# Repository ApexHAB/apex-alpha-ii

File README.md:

# Apex Alpha II
## A tiny, light-weight 'pico' flight computer with potential applications as a balloon neck payload

The flight computer is based around a CC430 microcontroller and radio by Texas Instruments with a uBlox Max-6.
It runs off a single AAA battery.

## Useful links

* [Homepage](http://www.apexhab.org) - http://www.apexhab.org
* [Apex Alpha II Homepage](http://www.apexhab.org/alpha-ii/) - http://www.apexhab.org/alpha-ii/
* [Contact](mailto:team@apexhab.org) - team@apexhab.org
* [Twitter](http://twitter.com/apexhab) - http://twitter.com/apexhab

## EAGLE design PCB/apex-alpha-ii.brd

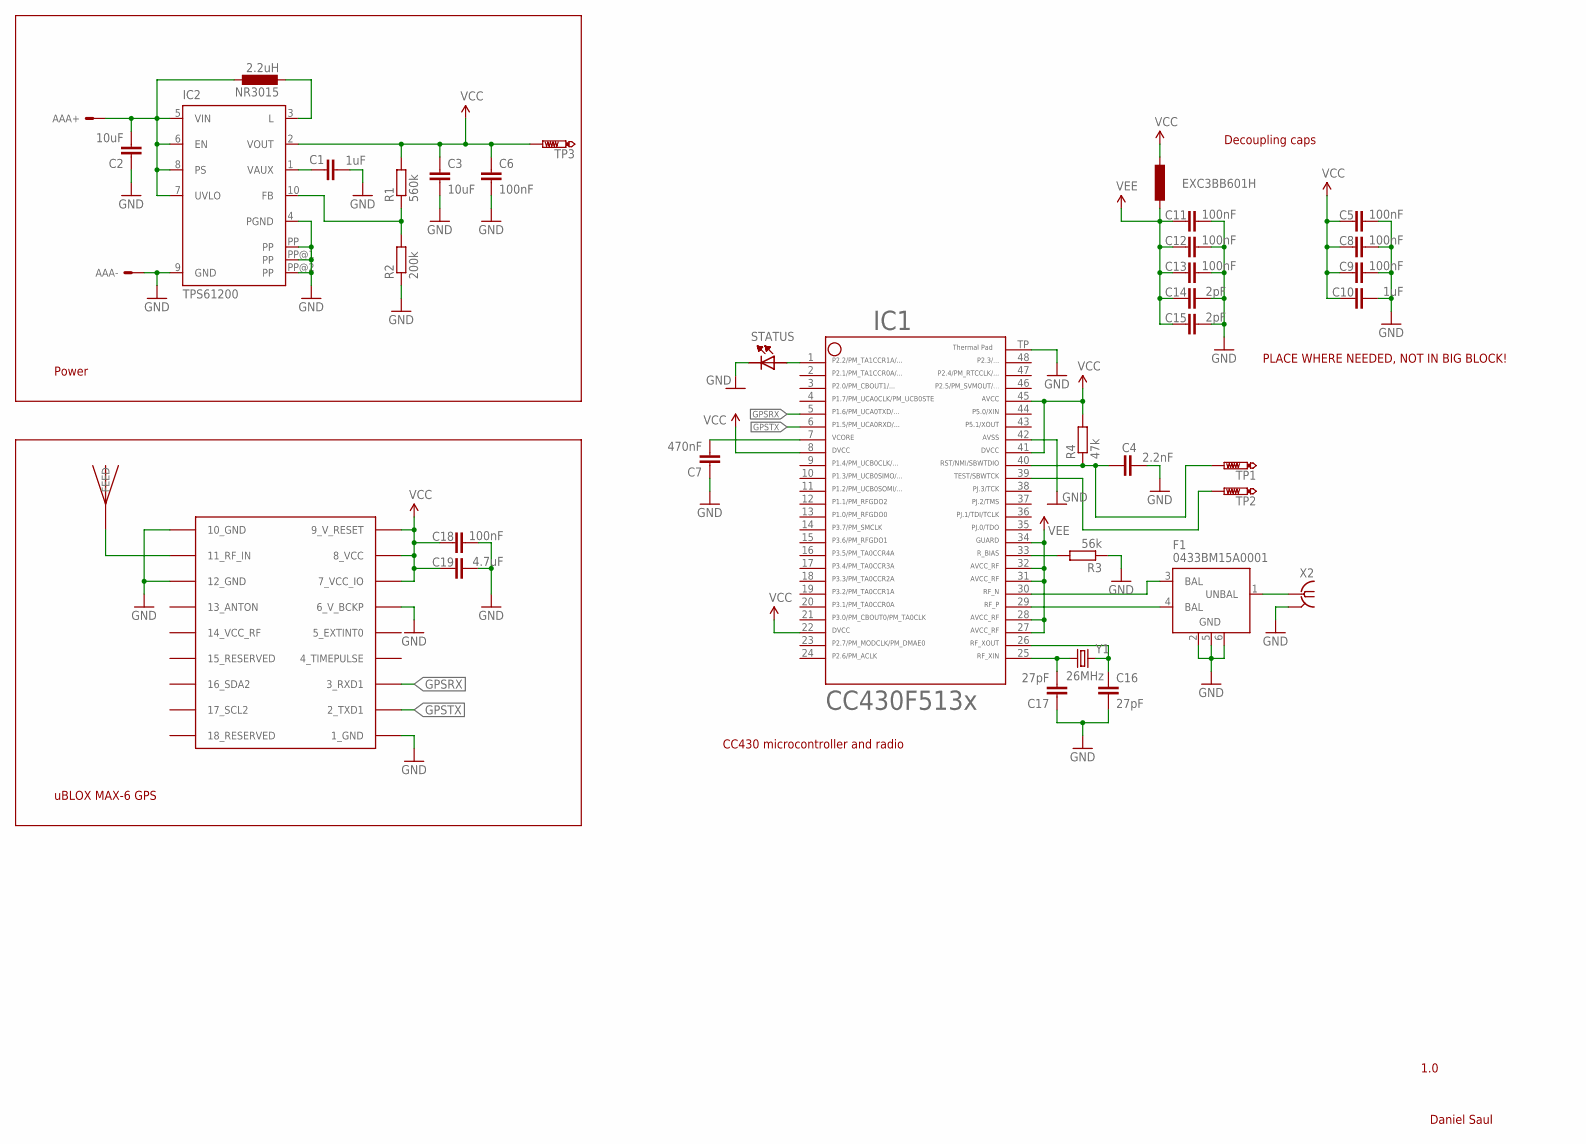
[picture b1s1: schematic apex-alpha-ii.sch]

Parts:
AAA: KEYSTONE-2466-THROUGH-HOLE-BATTERY-HOLDER-AAA; THROUGH-HOLE-BATTERY-HOLDER-AAA
C1, C10: 1uF; 0402-CAP
C2, C3: 10uF; 0805
C4: 2.2nF; 0402-CAP
C5, C6, C8, C9, C11, C12, C13, C18: 100nF; 0402-CAP
C7: 470nF; 0402-CAP
C14, C15: 2pF; 0402-CAP
C16, C17: 27pF; 0402-CAP
C19: 4.7uF; 0805
F1: 0433BM15A0001; 2450BM15A0002
GPS: UBLOX_MAX-6
IC1: CC430F5135; RGZ48
IC2: TPS61200; S-PDSO-N10
NR3015: 2.2uH; NR3015
R1: 560k; R0402
R2: 200k; R0402
R3: 56k; R0402
R4: 47k; R0402
TP1, TP2, TP3: PTR1B1,27; B1,27
U$1: JTI_ANTENNA-1575AT43A40
U$2: EXC3BB601H; R0603
U$3: STATUS; R0402
X2: SMA-142-0701-801/806; J502-ND-142-0701-801/806; MPN 142-0701-801
Y1: 26MHz; CRYSTAL-SMD-5X3

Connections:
GND: AAA.GND, C1.2, C2.1, C3.2, C4.2, C5.2, C6.2, C7.1, C8.2, C9.2, C10.2, C11.2, C12.2, C13.2, C14.2, C15.2, C16.2, C17.1, C18.2, C19.2, F1.2 (GND), F1.5 (GND), F1.6 (GND), GPS.1_GND, GPS.6_V_BCKP, GPS.10_GND, GPS.12_GND, IC1.42, IC1.TP (49), IC2.4 (PGND), IC2.9 (GND), IC2.PP, IC2.PP@1 (PP), IC2.PP@2 (PP), R2.1, R3.1, U$3.1 (C), X2.G@1 (GND), X2.G@2 (GND), X2.G@3 (GND), X2.G@4 (GND)
GPSRX: GPS.3_RXD1, IC1.5
GPSTX: GPS.2_TXD1, IC1.6
unnamed: AAA.+V, C2.2, IC2.5 (VIN), IC2.6 (EN), IC2.7 (UVLO), IC2.8 (PS), NR3015.P$1 (1)
unnamed: F1.3 (BAL), IC1.30
unnamed: IC2.3 (L), NR3015.P$2 (2)
unnamed: IC2.10 (FB), R1.1, R2.2
unnamed: C1.1, IC2.1 (VAUX)
unnamed: F1.4 (BAL), IC1.29
unnamed: F1.1 (UNBAL), X2.1
unnamed: GPS.11_RF_IN, U$1.FEED
unnamed: IC1.33, R3.2
unnamed: C7.2, IC1.7
unnamed: C4.1, IC1.40, R4.1, TP1.TP
unnamed: IC1.39, TP2.TP
unnamed: C17.2, IC1.25, Y1.1
unnamed: C16.1, IC1.26, Y1.3 (2)
unnamed: IC1.1, U$3.2 (A)
VCC: C3.1, C5.1, C6.1, C8.1, C9.1, C10.1, C18.1, C19.1, GPS.7_VCC_IO, GPS.8_VCC, GPS.9_V_RESET, IC1.8, IC1.22, IC1.41, IC1.45, IC2.2 (VOUT), R1.2, R4.2, TP3.TP, U$2.1
VEE: C11.1, C12.1, C13.1, C14.1, C15.1, IC1.27, IC1.28, IC1.31, IC1.32, IC1.34, U$2.2

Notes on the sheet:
1.0
Daniel Saul
Decoupling caps
Power
uBLOX MAX-6 GPS
CC430 microcontroller and radio
PLACE WHERE NEEDED, NOT IN BIG BLOCK!

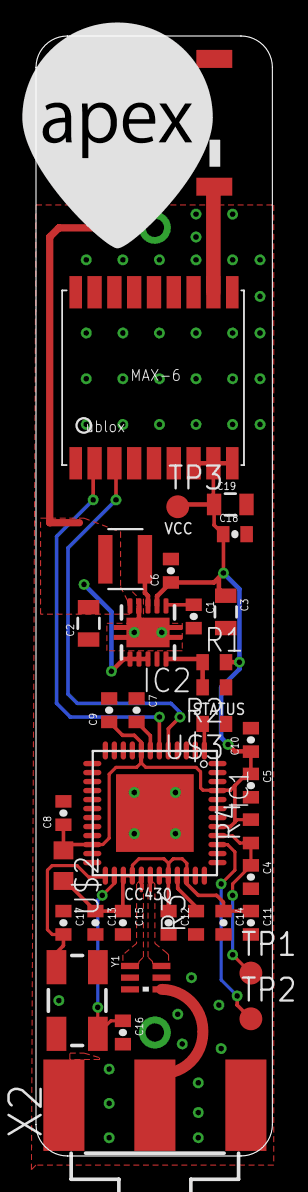
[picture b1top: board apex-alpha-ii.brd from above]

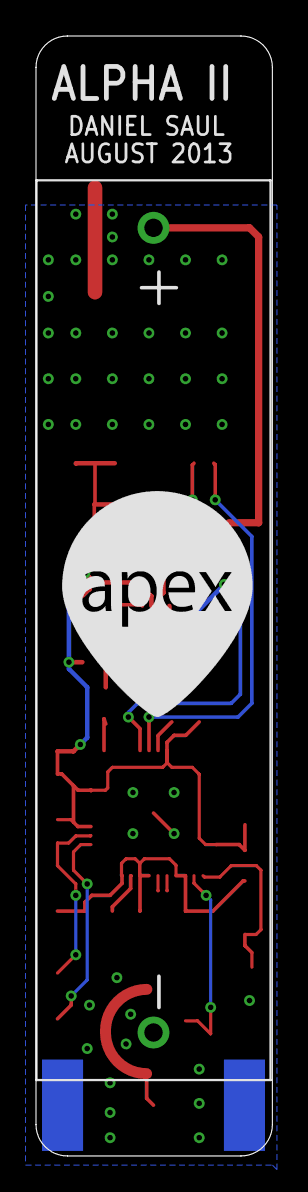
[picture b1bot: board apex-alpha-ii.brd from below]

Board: 2 copper layers, 13.1 x 62.2 mm, 39 parts (2 on the bottom side), 20 nets.

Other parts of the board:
U$4: APEX; APEXHAB-LOGO-SMALL
U$5: APEXHAB-LOGO-SMALL

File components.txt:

Farnell
============
26MHz crystal	 			1841998 or 1841997
Red 0805 1.85V LED  			1318244
Power Inductor NR3015 2.2uH  		1612110
Inductor EXC3BB601H  			1292697
Keystone AAA Battery Holder 2466  	1702632

433MHz Balun 0433BM15A0001 		2148531

10uF 0805 Capacitor (x2)		1828828
4.7uF 0805 Capacitor			1845769

1uF 0402 Capacitor (x2)			1288253		
100nF 0402 Capacitor (x8)		1288252
470nF 0402 Capacitor			8819726
2.2nF 0402 Capacitor			1414582
27pF 0402 Capacitor (x2)		1414584
2pF 0402 Capacitor (x2)			8771340

560k 0402 Resistor			2141009
200k 0402 Resistor			1469694
56k 0402 Resistor			2073131
47k 0402 Resistor			2073065

HAB Supplies
===========
uBlox MAX-6G (1.8V)
GPS Chip Antenna


Free Samples
===========
TI TPS61200
TI CC430F513x

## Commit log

2012-10-31 Initial farnell components to buy
2012-10-31 Schematic complete
2012-12-27 Started board - battery positive under ublox, negative under radio
2012-12-27 Flipped battery - still AAA
2012-12-27 Changed to TLV70019 linear reg for a 3V battery
2012-12-27 Replaced AAA holder with CR123A holder
2012-12-27 Renamed to CR123a version
2012-12-27 AAA version fully laid out.
2012-12-28 Ground planes. Started routing.
2012-12-29 Nearly finished routing... committing before I lose it all.
2012-12-29 Finished! I think.
2012-12-29 Added huge image of board
2013-08-08 New PCB layout etc.
2013-08-12 Final PCB layout
2013-08-12 Started full component list
2013-08-13 Updated component list
2013-08-13 Generated gerbers
2013-08-13 Removed component names from silkscreen

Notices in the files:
parts and their libraries:
SparkFun: Licensing: CC v3.0 Share-Alike You are welcome to use this library for commercial purposes.
